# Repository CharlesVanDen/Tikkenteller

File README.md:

# Tikkenteller
Repurpose an old PTT tikkenteller to function as a general electromechanical counter.
https://www.youtube.com/watch?v=D_D3LM-WEwQ&feature=youtu.be

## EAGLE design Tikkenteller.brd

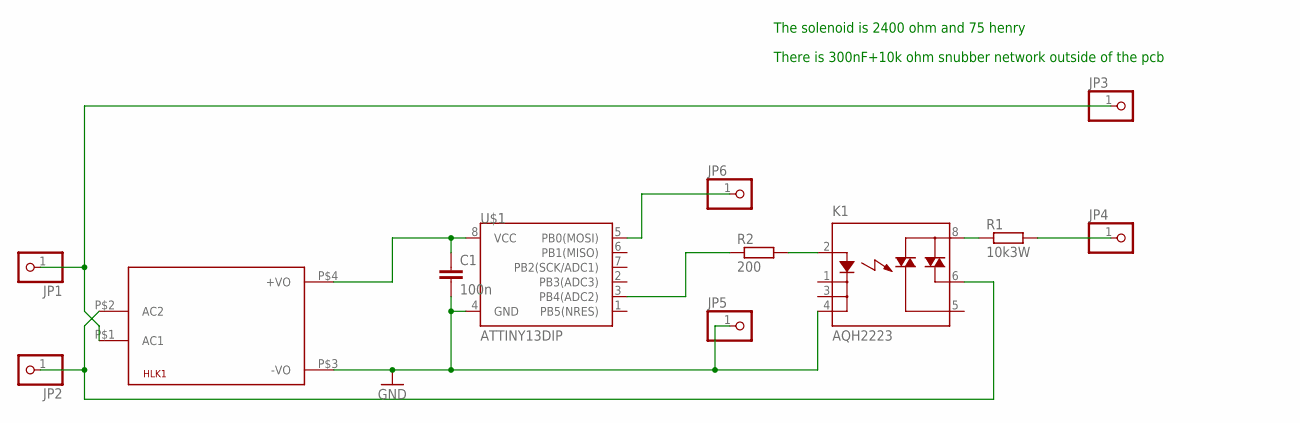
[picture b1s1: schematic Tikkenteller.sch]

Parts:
C1: 100n; C050-024X044
HLK1: HLK-PM013W; HLK-PM01
JP1, JP2, JP3, JP4, JP5, JP6: PINHD-1X1; 1X01
K1: AQH2223; DIL07
R1: 10k3W; RESISTOR10
R2: 200; RESISTOR4
U$1: ATTINY13DIP; DIP08

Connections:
GND: C1.2, HLK1.P$3 (-VO), JP5.1, K1.4 (K2), U$1.4 (GND)
unnamed: HLK1.P$2 (AC2), JP2.1, K1.6 (DS3)
unnamed: HLK1.P$1 (AC1), JP1.1, JP3.1
unnamed: K1.8 (DS1), R1.1
unnamed: JP4.1, R1.2
unnamed: K1.2 (A), R2.2
unnamed: R2.1, U$1.3 (PB4(ADC2))
unnamed: C1.1, HLK1.P$4 (+VO), U$1.8 (VCC)
unnamed: JP6.1, U$1.5 (PB0(MOSI))

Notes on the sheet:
There is 300nF+10k ohm snubber network outside of the pcb
The solenoid is 2400 ohm and 75 henry

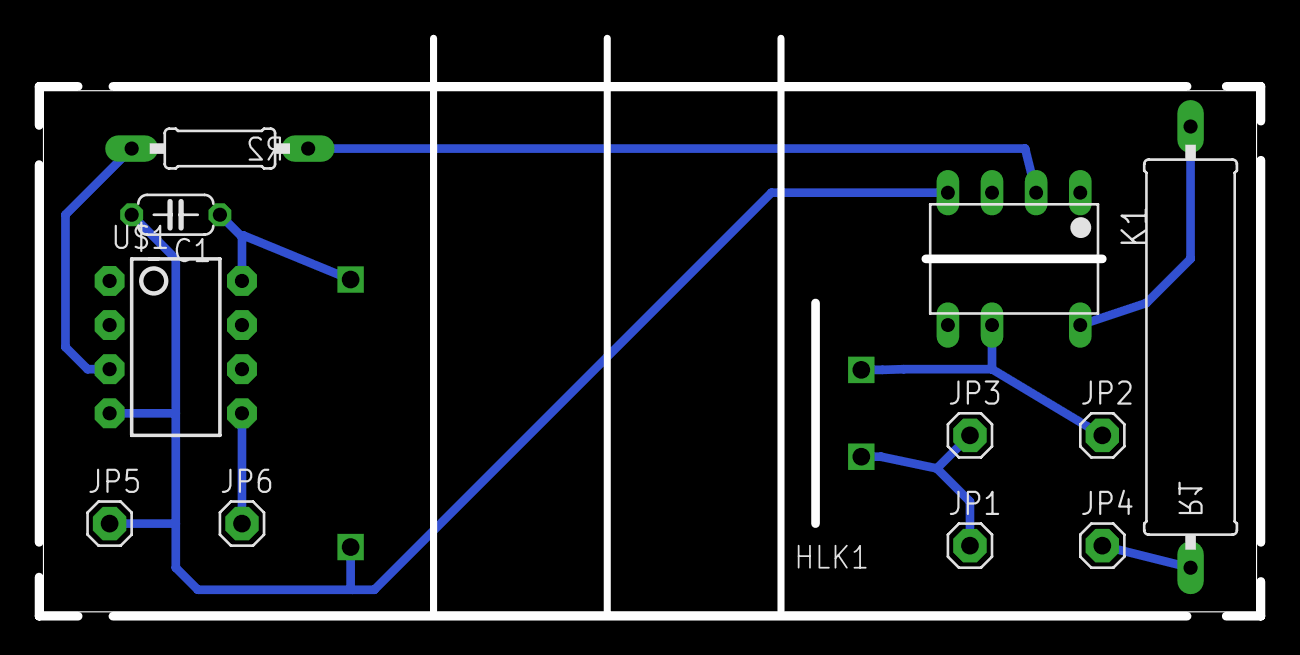
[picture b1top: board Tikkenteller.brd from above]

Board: 2 copper layers, 69.8 x 30.0 mm, 12 parts (0 on the bottom side), 9 nets.

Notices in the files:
parts and their libraries:
SparkFun-DigitalIC: Licensing: Creative Commons ShareAlike 4.0 International - https://creativecommons.org/licenses/by-sa/4.0
